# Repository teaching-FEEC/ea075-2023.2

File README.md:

# EA075 - Introdução a Projeto de Sistemas Embarcados

2° Semestre de 2023

Profa. Paula Dornhofer Paro Costa

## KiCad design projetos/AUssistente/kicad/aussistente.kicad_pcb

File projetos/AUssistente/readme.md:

# `AUssistente`
# `Pet Care Assistant`

## Apresentação

O presente projeto foi originado no contexto das atividades da disciplina de graduação *EA075 - Introdução ao Projeto de Sistemas Embarcados*, 
oferecida no segundo semestre de 2023, na Unicamp, sob supervisão da Profa. Dra. Paula Dornhofer Paro Costa, do Departamento de Engenharia de Computação e Automação (DCA) da Faculdade de Engenharia Elétrica e de Computação (FEEC).

## Integrantes

|Nome  | RA | Curso|
|--|--|--|
| Betania Eugenia Rodrigues da Silva  | 167508  | Eng. Elétrica|
| Vinícius de Oliveira Peixoto Rodrigues  | 245294  | Eng. de Computação |

## Descrição do Projeto
> Descrição do objetivo principal do projeto, incluindo contexto gerador, motivação.

O objetivo do presente projeto é desenvolver um sistema que auxilie os donos de animais de estimação, com foco em cães e gatos, a facilitar o monitoramento da saúde de seus pets em tempo real. Esta iniciativa surge em resposta à crescente demanda por cuidados mais especializados e personalizados para nossos queridos animais de estimação, que estão cada vez mais integrados à vida familiar. O sistema atuará como um 'companheiro canino e felino inteligente', oferecendo uma solução completa para monitorar e melhorar o bem-estar de nossos bichinhos, garantindo que eles desfrutem de uma vida feliz e saudável ao nosso lado.

> Qual problema vocês pretendem solucionar?

Nosso projeto tem como objetivo resolver diversos desafios enfrentados pelos donos de animais de estimação. O primeiro grande problema a ser abordado é a perda de animais de estimação quando eles escapam, o que é uma preocupação frequente para muitos proprietários. Para resolver essa questão, haverá um sistema de geolocalização que permite localizar os animais rapidamente, facilitando o reencontro com seus donos.

Além disso, nosso sistema visa melhorar o cuidado com a saúde dos animais de estimação de maneira mais abrangente. Ele monitorará constantemente os batimentos cardíacos dos animais e notificará os proprietários se os batimentos cardíacos saírem do normal, permitindo uma resposta rápida em caso de problemas de saúde. Além do mais, o sistema será capaz de aferir o sono e o padrão de alimentação dos animais, o que ajuda os donos a garantir que seus bichinhos tenham um estilo de vida saudável. Isso não só aumenta a qualidade de vida dos animais de estimação, mas também antecipa possíveis agravantes para sua saúde, permitindo intervenções precoces quando necessário.

> Quem são os potenciais usuários?
 
Donos de animais de estimação em um geral.
 
> É possível estabelecer um valor econômico associado?

Sim, é possível, mas primeiramente é necessário realizar um levantamento dos componentes a serem utilizados.

## Descrição Funcional

### Funcionalidades
- Rastreamento de GPS
- Comunicação via BLE/rede sem fio
- Monitoramento de batimentos cardíacos e oxigenação sanguínea
- Acompanhamento dos Níveis de Atividades
- Aferição de Hábitos Diários como frequência e nutrição das refeições e padrões de sono
- Alertas de saída da área pré determinada pelo dono
- Alertas de temperatura corporal do pet
- Análise dos dados diários através gráficos para melhor entendimento do dono

### Configurabilidade

- Pareamento BLE: o dispositivo pode ser configurado por meio de um botão para se conectar a um dispositivo (smartphone, assistente virtual, etc.) por Bluetooth para transmitir dados
- Perfil de energia: o modo de funcionamento do dispositivo pode ser configurado de modo a controlar o consumo de energia, prolongando assim o tempo de atividade antes de ser necessário carregar o aparelho

### Eventos
- Ativação do botão de ligar/desligar
- Leitura de sensores (feitas por meio de interrupção de hardware): os sensores serão configurados para, em intervalos regulares, reportarem para o microcontrolador os valores medidos. Estimativa dos intervalos de leituras:
    - Sensor inercial (IMU): entre 200ms e 2s
    - Sensor de batimentos cardíacos/oxigenação sanguínea: entre 1s e 10s
    - Sensor de temperatura: entre 15s e 1m
    - Sensor de nível de bateria: entre 15s e 1m
    - GPS: entre 15s e 1m
- Ativação do botão de pareamento BLE
- Requisição recebida por BLE
- Valores críticos de batimento cardíaco/oxigenação/temperatura
- Fuga do pet (saída da área pré-determinada pelo dono)
- Nível crítico de bateria

### Tratamento de Eventos
- Ativação do botão de ligar/desligar
    - Dispositivo desligado ou em _deep sleep_: carrega dados de configuração da memória flash ou da SRAM, realiza o boot e o bringup dos componentes
    - Dispositivo ativo ou _idle_: realiza a rotina de shutdown, escrevendo dados relevantes na memória não-volátil e desligando a placa

- Leitura de sensores: armazena os dados em um buffer circular na memória RAM
    - Caso o buffer circular esteja cheio: armazena os dados na SRAM ou na memória não-volátil

- Ativação do botão de pareamento BLE: executa a rotina de pareamento para se conectar ao smartphone

- Requisição recebida por BLE/rede sem fio: invoca a rotina adequada para responder à requisição de maneira assíncrona (sem interromper o fluxo de leitura de sensores)

- Valores críticos de batimento cardíaco/oxigenação/temperatura e fuga de pet: toca um aviso sonoro e envia uma mensagem de alerta para o dispositivo conectado por Bluetooth/rede wireless (caso haja um)

- Nível crítico de bateria: envia uma mensagem de alerta para o dispositivo conectado por Bluetooth, escreve dados relevantes na SRAM, desativa os sensores e entra em _deep sleep_

## Descrição Estrutural do Sistema

## Especificações

### Especificação Estrutural

#### Tabela de componentes
| Componente    | Descrição | Funcionalidades | Interface de comunicação | Datasheet |
| ----------    | --------- |    ---------    |         ---------        |  -------  |
| ESP32-U4WDH   | Microcontrolador | Wi-Fi + BLE; excelente gerenciamento de energia; suporte a UART/I2C/SPI; memória flash SPI de 4MB integrada | - | [esp32.pdf](datasheets/esp32.pdf) |
| TMP117        | Sensor digital de temperatura | Alta precisão + baixo consumo de energia| I2C | [tmp117.pdf](datasheets;tmp117.pdf) |
| MAX30102      | Oxímetro + sensor de batimentos | Baixo consumo de energia, resistência a estresse mecânico | I2C | [max30102.pdf](datasheets/max30102.pdf) |
| MAX17043      | Medidor de carga de bateria | Baixo consumo de energia, alta precisão de medição | I2C | [max17043.pdf](datasheets/max17043.pdf) |
| BMI270        | Unidade de medida inercial (IMU) de 6 eixos | Baixo consumo de energia; correção de erro integrada em hardware | I2C/SPI | [bmi270.pdf](datasheets/bmi270.pdf) |
| MAX-M10S      | GPS | Baixo consumo de energia, alta precisão, monitoramento contínuo de geoposicionamento | UART/I2C | [max-m10s.pdf](datasheets/max-ma10s.pdf)

#### Características de operação

| Parâmetro | Min. | Típico | Máx. | Unidade |
| --------  |  --  |  --  | ------ |  -----  |
| Tensão de alimentação | 3.0 | 3.3 | 3.6 | V |
| Capacidade de corrente da bateria | 0.5 | - | - | A |
| Temperatura | -30 | - | 125 | °C |

#### Limites absolutos de operação

Estresse acima dos limites da tabela abaixo podem causar dano permanente ao dispositivo.

| Parâmetro | Min. | Máx. | Unidade |
| --------  |  --  |  --  |  -----  |
| Tensão de entrada | -0.3  | 3.6 | V |
| Corrente | - | 1200 | mA |
| Temperatura | -50 | 150 | °C |
| Impacto mecânico | - | 20000 | g |
| Queda livre sobre superfícies rígidas | - | 1.8 | m |

#### Interfaces de periféricos planejadas

Será necessário projetar um barramento I2C com características elétricas adequadas, seguindo as recomendações
da [especificação oficial](https://www.nxp.com/docs/en/user-guide/UM10204.pdf) do protocolo, no qual os periféricos
serão conectados de modo a atuar como targets, com a MCU assumindo o papel de controller.

Será necessário também projetar um _buzzer_ piezoelétrico de modo a tocar os alertas sonoros especificados nos algoritmos
de tratamento de eventos.

### Especificação de Algoritmos 

Para podermos tratar os eventos decorrentes do sistema do AUssistente, desenvolvemos o seguinte algoritmo em pseudocódigo.

```text
AUssistente;
timer_sensor_inercial;
timer_sensor_batimento;
timer_sensor_temperatura;
timer_sensor_bateria;
timer_gps;
buffer_circular;

função principal():
  em caso de evento:
		  processar_evento(evento)

função processar_evento(evento):
  caso evento == evento.botao_ligar:
		  se AUssistente.estado == estado.desligado || AUssistente.estado == estado.hibernar:
      configs = carregar_dados_configuracao( )
      inicializar_componentes(configs)

  senão, se AUssistente.estado == estado.ativo || AUssistente.estado == estado.ocioso:
    salvar_dados( )
    desligar_placa( )

  caso evento == evento.leitura_sensor:
		  dados = ler_sensor(evento.enum_sensor)
    se buffer_circular está cheio:
      salvar_memoria(dados)
		  senão:
      buffer_circular[dados.enum_sensor].proximo(dados.info)

  caso evento == evento.pareamento:
    AUssistente.dispositivo = parear( )

  caso evento == evento.requisicao:
    tratar_requisicao(evento.requisicao)

  caso evento == evento.valores_criticos:
    tocar_aviso_sonoro(evento.valor)
    enviar_mensagem_dispositivo(evento.valor)

  caso evento == evento.bateria_critica:
    enviar_alerta_bateria( )
    salvar_dados( )
    desativar_sensores( )
    hibernar( )

  caso default:
    emitir_erro_evento()

função carregar_dados_configuracao():
  configs = ler_arquivo(caminho_arquivo)
  retornar configs

função inicializar_componentes(configs):
  AUssistente = novo AUssistente;
  novo buffer_circular = [5][configs[tamBuffer]]
  AUssistente.perfil_energia = configs[pEnergia]
  AUssistente.ultimo_dispositivo = configs[ultimoDispositivoConectado]
  AUssistente.sensores_ativos = true
  timer_gps = configs[tGPS] ? configs[tGPS] : 30s
  timer_sensor_bateria = configs[tBateria] ? configs[tBateria] : 30s
  timer_sensor_batimento = configs[tBatimento] ? configs[tBatimento] : 5s
  timer_sensor_inercial = configs[tIMU] ? configs[tIMU] : 1s
  timer_sensor_temperatura = configs[tTemperatura] ? configs[tTemperatura] : 30s
  AUssistente.dispositivo = parear(AUssistente.ultimo_dispositivo)

função salvar_dados():
  escrever(caminho_arquivo, AUssistente, buffer_circular)

função desligar_placa():
  power_off_mode()

função ler_sensor(sensor_id):
  retornar pegar_leitura_sensor(sensor_id)

função salvar_memoria(dados):
  EEPROM.write(dados);

função parear(dispositivo):
  BTSerial.begin(dispositivo.serial)
  sucesso = BTSerial.available()
	 retornar sucesso ? dispositivo : null

função parear():
  device = BTSerial.emparelhar()
	 retornar device

função tratar_requisicao(requisicao):
	 caso requisicao == requisicao.1:
		  tratamento_1()
	 caso requisicao == requisicao.2:
		  tratamento_2()
	 caso default:
		  tratamento_default()

função tocar_aviso_sonoro(tipo):
	 tone(buzzer_pin, tipo * 800)
	 delay(15000)
	 noTone(buzzer_pin)

função enviar_mensagem_dispositivo(tipo):
	 BTSerial.write("Atenção: O " + tipo + " está com valores criticos!")

função enviar_alerta_bateria():
	 BTSerial.write("Atenção: Bateria do AUssistente em niveis criticos, entrando em hibernação...")

função desativar_sensores():
	 AUssistente.sensores_ativos = false

função hibernar():
	 power_save_mode()

```

## Referências (ATUALIZAR SE NECESSÁRIO)
- Especificação do protocolo I2C https://www.nxp.com/docs/en/user-guide/UM10204.pdf
- Cálculos de valores de resistência em barramentos I2C https://www.allaboutcircuits.com/technical-articles/the-i2c-bus-hardware-implementation-details/
- Design de buzzers piezoelétricos https://www.diodes.com/assets/App-Note-Files/Design-Considerations-for-Driving-Piezoelectric-Buzzers.pdf
- Roteamento de bus I2C https://hillmancurtis.com/i2c-pcb-layout/

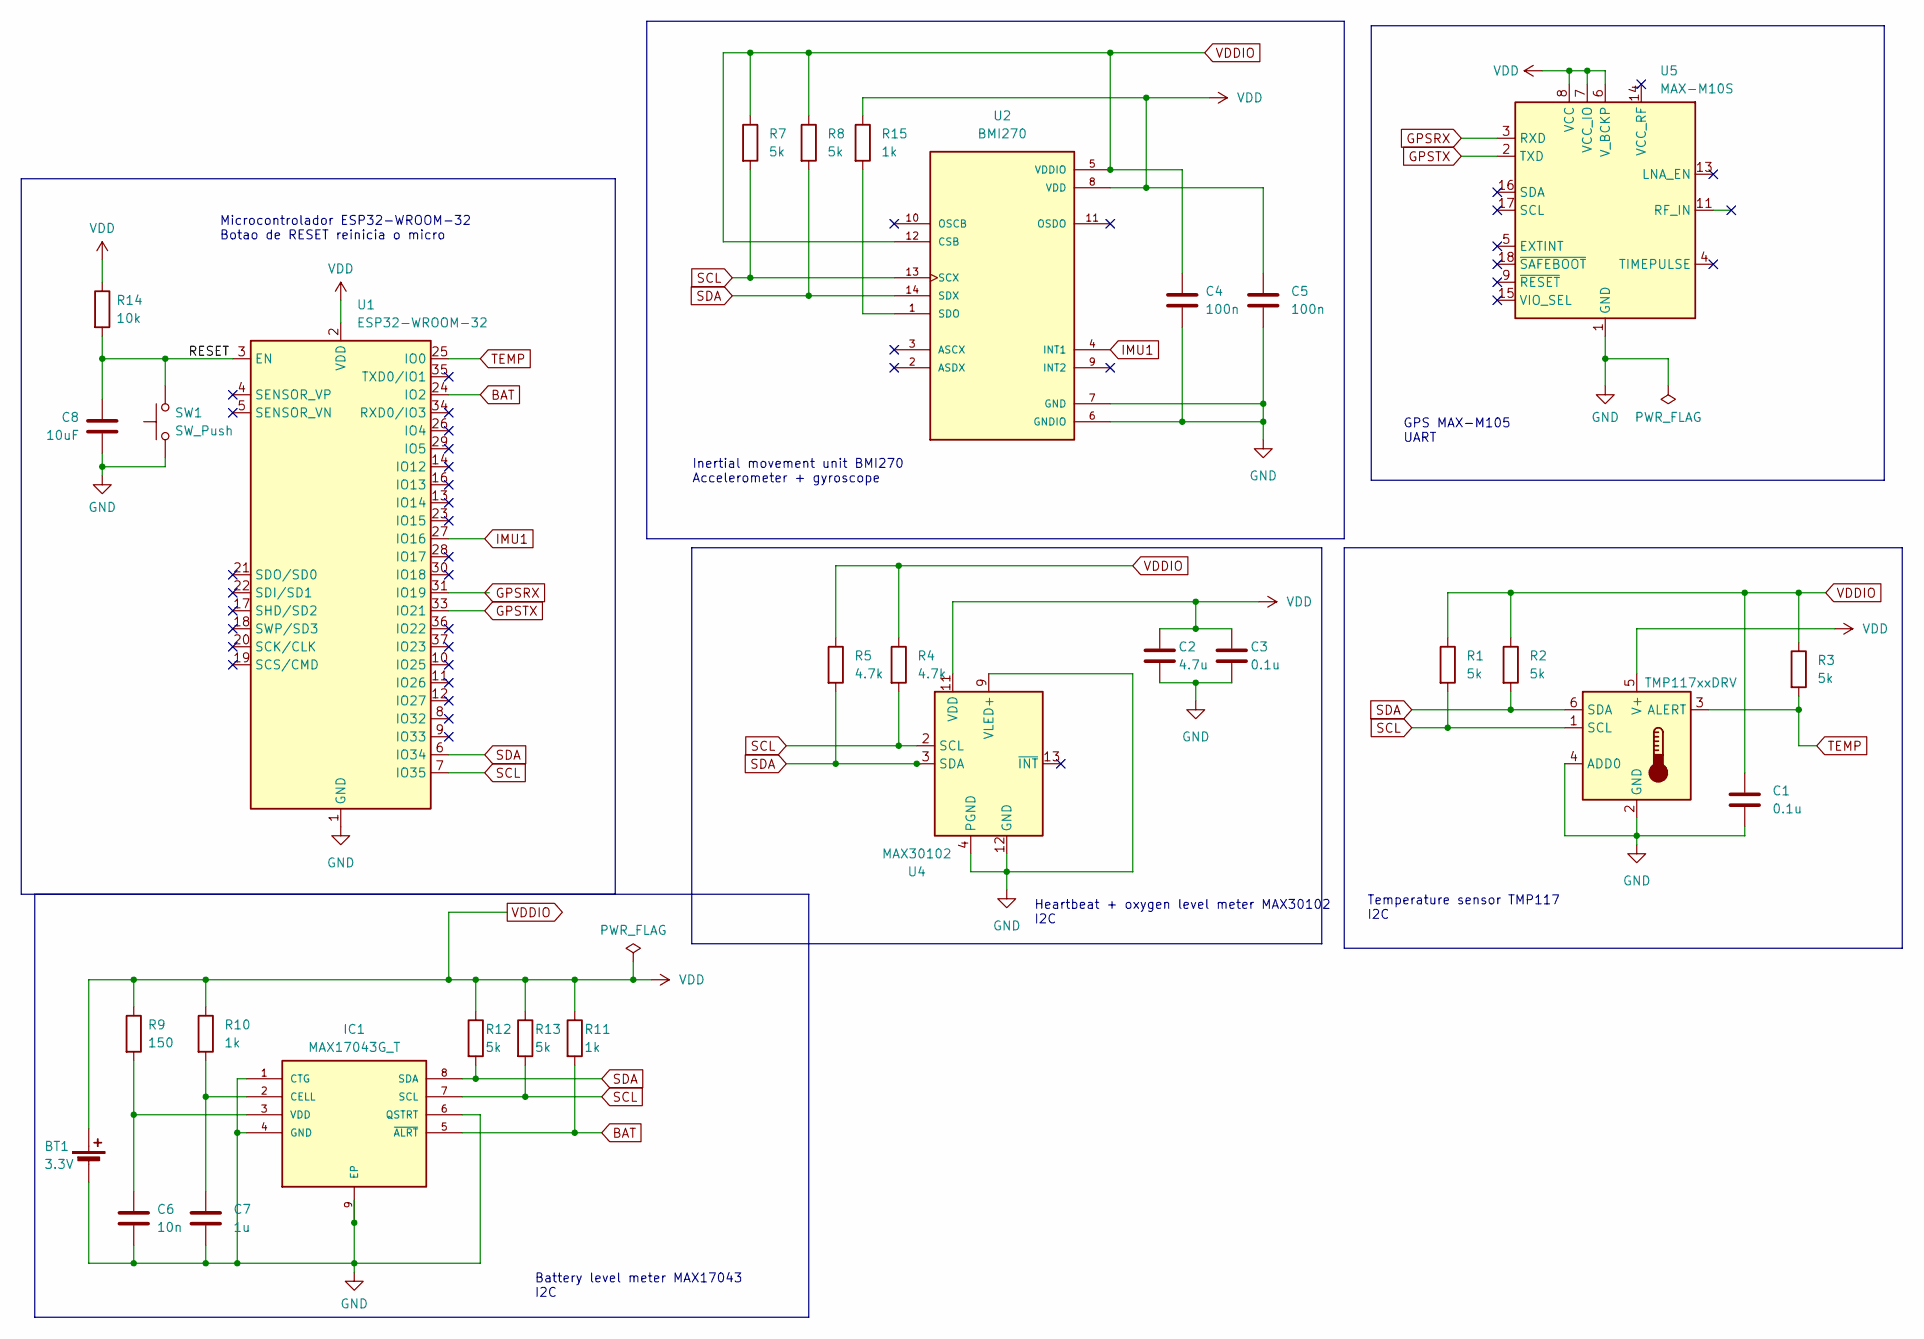
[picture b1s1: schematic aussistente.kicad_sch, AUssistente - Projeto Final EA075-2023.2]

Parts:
BT1: 3.3V; BatteryHolder_Eagle_12BH611-GR
C1, C3: 0.1u; C_0402_1005Metric
C2: 4.7u; C_0402_1005Metric
C4, C5: 100n; C_0402_1005Metric
C6: 10n; C_0402_1005Metric
C7: 1u; C_0402_1005Metric
C8: 10uF; C_0402_1005Metric
IC1: MAX17043G_T; SON50P300X200X80-9N; MOUSER_PART_NUMBER 700-MAX17043G+T; DigiKey_Part_Number 175-MAX17043G+TTR-ND
R1, R2, R3, R7, R8, R12, R13: 5k; R_0201_0603Metric
R4, R5: 4.7k; R_0201_0603Metric
R9: 150; R_0201_0603Metric
R10, R11, R15: 1k; R_0201_0603Metric
R14: 10k; R_0201_0603Metric
SW1: SW_Push; SW_PUSH_6mm_H5mm
U1: ESP32-WROOM-32
U2: BMI270; XDCR_BMI270
U3: TMP117xxDRV; WSON-6-1EP_2x2mm_P0.65mm_EP1x1.6mm
U4: MAX30102; Maxim_OLGA-14_3.3x5.6mm_P0.8mm
U5: MAX-M10S; ublox_MAX

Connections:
/RESET: C8.1, R14.2, SW1.2, U1.3 (EN)
BAT: IC1.5 (~ALRT), R11.2, U1.24 (IO2)
GND: BT1.2 (-), C1.1, C2.2, C3.2, C4.2, C5.2, C6.2, C7.2, C8.2, IC1.1 (CTG), IC1.4 (GND), IC1.6 (QSTRT), IC1.9 (EP), SW1.1, U1.1 (GND), U1.15 (GND), U1.38 (GND), U1.39 (GND), U2.6 (GNDIO), U2.7 (GND), U3.2 (GND), U3.4 (ADD0), U4.4 (PGND), U4.9 (VLED+), U4.10 (VLED+), U4.12 (GND), U5.1 (GND), U5.10 (GND), U5.12 (GND)
GPSRX: U1.31 (IO19), U5.3 (RXD)
GPSTX: U1.33 (IO21), U5.2 (TXD)
IMU1: U1.27 (IO16), U2.4 (INT1)
unnamed: C7.1, IC1.2 (CELL), R10.2
unnamed: C6.1, IC1.3 (VDD), R9.2
unnamed: R15.2, U2.1 (SDO)
SCL: IC1.7 (SCL), R1.2, R4.2, R7.2, R13.2, U1.7 (IO35), U2.13 (SCX), U3.1 (SCL), U4.2 (SCL)
SDA: IC1.8 (SDA), R2.2, R5.2, R8.2, R12.2, U1.6 (IO34), U2.14 (SDX), U3.6 (SDA), U4.3 (SDA)
TEMP: R3.2, U1.25 (IO0), U3.3 (ALERT)
VDDIO: BT1.1 (+), C1.2, C2.1, C3.1, C4.1, C5.1, R1.1, R2.1, R3.1, R4.1, R5.1, R7.1, R8.1, R9.1, R10.1, R11.1, R12.1, R13.1, R14.1, R15.1, U1.2 (VDD), U2.5 (VDDIO), U2.8 (VDD), U2.12 (CSB), U3.5 (V+), U4.11 (VDD), U5.6 (V_BCKP), U5.7 (VCC_IO), U5.8 (VCC)

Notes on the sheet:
Microcontrolador ESP32-WROOM-32 Botao de RESET reinicia o micro
Battery level meter MAX17043 I2C
Heartbeat + oxygen level meter MAX30102 I2C
GPS MAX-M105 UART
Temperature sensor TMP117 I2C
Inertial movement unit BMI270 Accelerometer + gyroscope

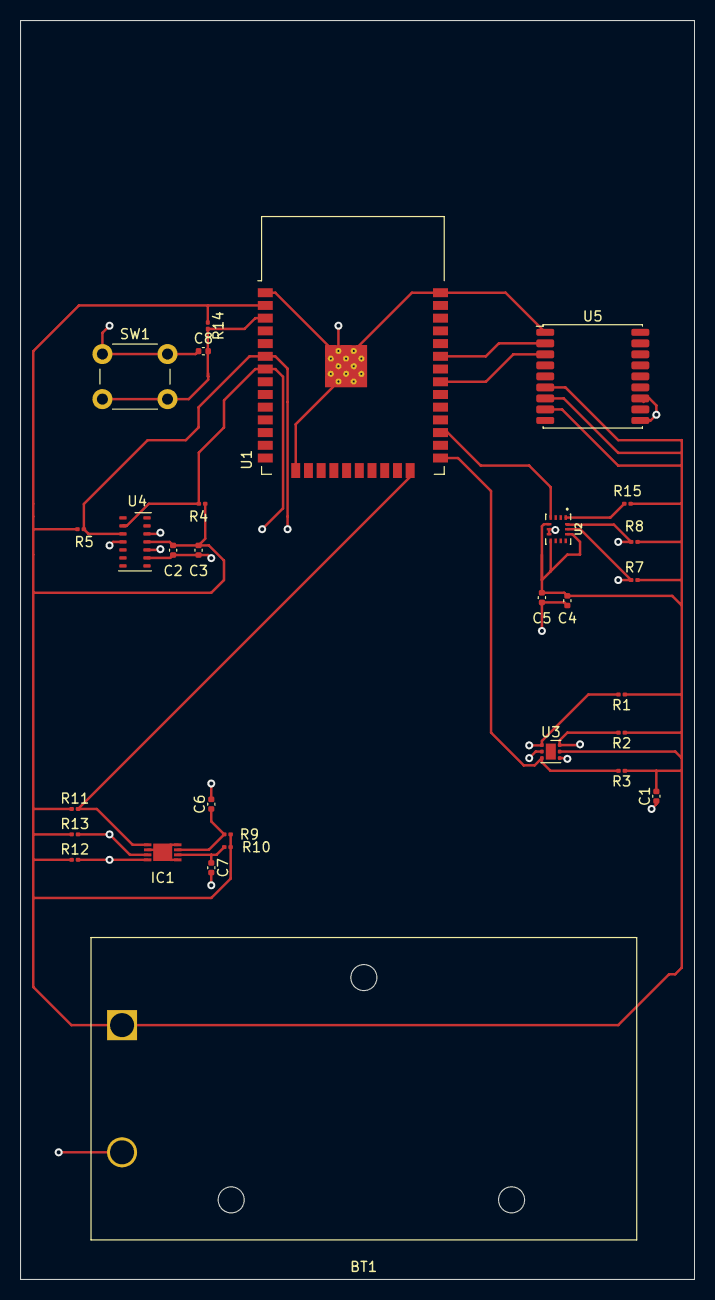
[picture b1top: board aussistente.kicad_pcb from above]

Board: 4 copper layers, 67.3 x 125.7 mm, 30 parts (0 on the bottom side), 13 nets.

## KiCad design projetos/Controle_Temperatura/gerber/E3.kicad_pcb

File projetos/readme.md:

Crie sua pasta de projetos aqui.

Faça edições e adicione arquivos apenas em sua pasta de projetos.

:warning: Não altere este arquivo este arquivo readme.md

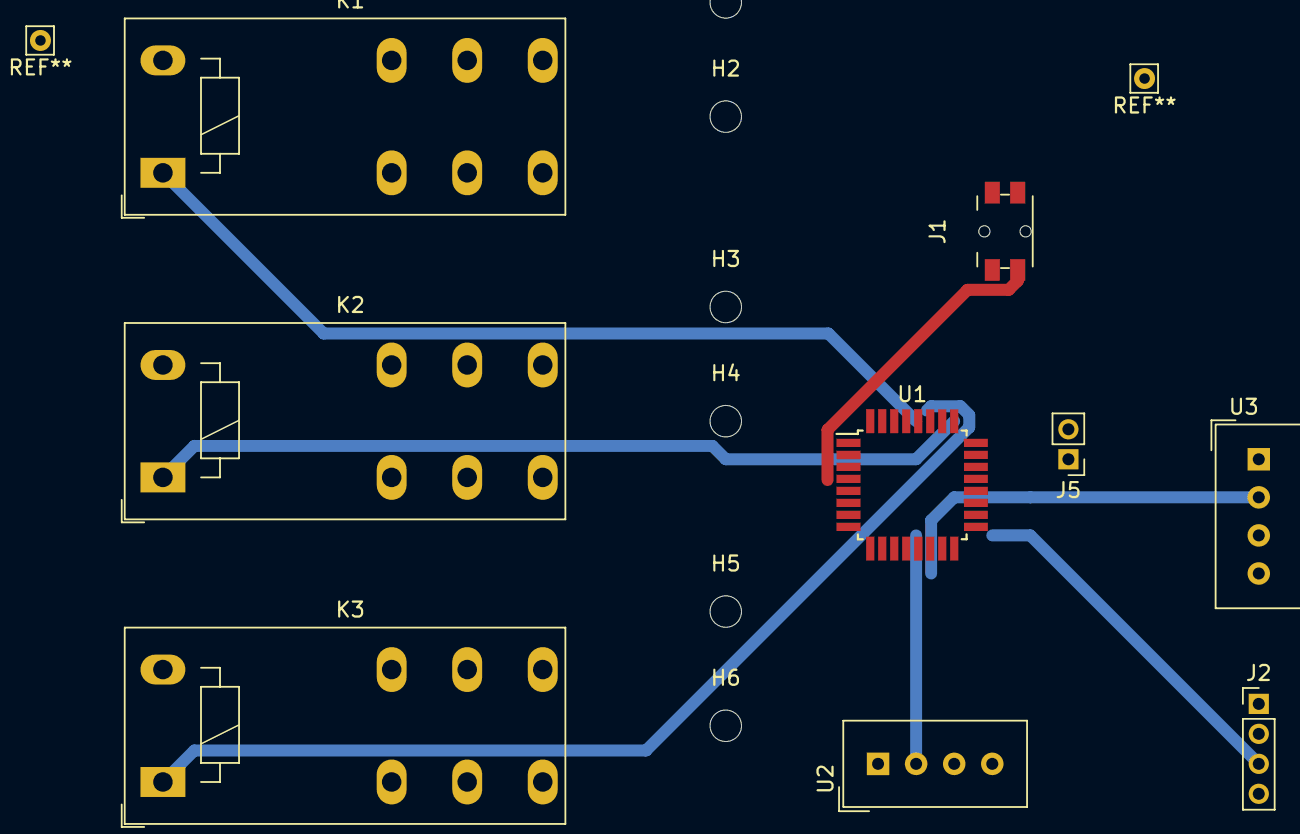
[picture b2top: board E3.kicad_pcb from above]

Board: 4 copper layers, 15 parts (0 on the bottom side), 10 nets.

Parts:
H1: +Motor; MountingHole_2.1mm
H2: -Motor; MountingHole_2.1mm
H3: +Condicionador de Ar; MountingHole_2.1mm
H4: -Condicionador de Ar; MountingHole_2.1mm
H5: +Umidificador; MountingHole_2.1mm
H6: -Umidificador; MountingHole_2.1mm
J1: Botao Iniciar; Panasonic_EVQPUM_EVQPUD
J2: Rain_Inputs; PinHeader_1x04_P2.00mm_Vertical
J5: Sensor fim de curso; PinHeader_1x02_P2.00mm_Vertical
K1, K2, K3: RT314A24; Relay_SPDT_Schrack-RT1-16A-FormC_RM5mm
U1: ATmega328-A; TQFP-32_7x7mm_P0.8mm
U2, U3: DHT11; Aosong_DHT11_5.5x12.0_P2.54mm

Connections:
Earth: J2.2, J5.1, U1.16 (PB4), U2.4 (GND), U3.4 (GND)
unnamed: J1.2, J2.1, J5.2, U1.4 (VCC), U1.6 (VCC), U2.1 (VDD), U3.1 (VDD)
unnamed: K1.A2, K2.A2, K3.A2, U1.3 (GND), U1.5 (GND), U1.21 (GND)
unnamed: J1.1, U1.25 (PC2)
unnamed: J2.3, U1.17 (PB5)
unnamed: U1.12 (PB0), U2.2 (DATA)
unnamed: U1.13 (PB1), U3.2 (DATA)
unnamed: K2.A1, U1.26 (PC3)
unnamed: K1.A1, U1.27 (PC4)
unnamed: K3.A1, U1.28 (PC5)

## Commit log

2023-07-30 Alterações readme para novo semestre
2023-07-30 Alterações readme novo semestre
2023-07-30 Criação de novo readem
2023-07-30 Criação readme exemplo
2023-09-07 Diagrama_black_box.drawio
2023-09-07 Rascunho inicial do README
2023-09-07 Actualizar Diagrama_black_box.drawio
2023-09-07 Adicionado Diagrama_black_box.drawio.png
2023-09-07 Actualizar Diagrama_black_box.drawio.png
2023-09-07 Descrição do Sistema Black Box para entrega 1
2023-09-07 project description and functional description
2023-09-07 fixing spaces
2023-09-07 Adding references
2023-09-07 Correção de formatação, e adiçao de tópicos
2023-09-07 modificando referencias
2023-09-07 Atualizar curso
2023-09-07 adicionando uma referencia
2023-09-07 resolving git problems
2023-09-08 update diagrama
2023-09-08 Create nosso_projeto
2023-09-09 Titulo do projeto
2023-09-09 Descrição_Estrutural.drawio
2023-09-09 inserção do ra e nome
2023-09-09 Adicionado Descrição_Estrutural.drawio
2023-09-09 removendo diagrama antigo
2023-09-10 Inserção da Descrição do projeto, Descrição Funcional, Funcionalidades, Configurabilidade, Eventos e Tratamento de Eventos
2023-09-10 Inserção de quebra de linha
2023-09-10 Update readme.md
    1° edição
2023-09-10 chocadeira.drawio
2023-09-10 Projeto Cobertor Térmico
    Versão inicial
2023-09-10 Commit sem draw.io
2023-09-10 Adicionado chocadeira.drawio.png
2023-09-10 tratamento de eventos e referências
2023-09-10 Entrega 01
2023-09-10 Criando estrutura
2023-09-10 Adicionar evento
2023-09-10 Adicionar tratamento de eventos
2023-09-10 Fix typo
2023-09-10 Add diagram
2023-09-10 Adicionar diagrama
2023-09-10 Add diagram with background
2023-09-10 Create Final Project
2023-09-10 Create Sketch
    First archive
2023-09-10 criar-proj
2023-09-10 Update readme.md and add datasheets
2023-09-10 adicionando descrição estrutural
2023-09-10 Adicionado Descrição_Estrutural.png
2023-09-10 descricao
2023-09-10 econômica
2023-09-10 Update eventos
2023-09-10 tratar display
2023-09-10 Adicionado regador_flowchart.drawio
2023-09-10 Actualizar regador_flowchart.drawio
2023-09-10 Added regador_flowchart.drawio
2023-09-10 Add new events to readme
2023-09-10 Added regador_flowchart.png
2023-09-10 Update refs
2023-09-10 adding refs
2023-09-11 funcionalidades
2023-09-11 configura
2023-09-11 corre
2023-09-11 eventos
2023-09-11 conf
2023-09-11 Update and rename readme.md to ea075-E1.md
    update do texto
2023-09-11 E1-EA075-E1.md
2023-09-11 Add structural diagram
2023-09-11 E1-EA075.md
2023-09-11 2023.1_EA075_E1.md
2023-09-11 upload primeira entrega Beatriz e Emily
2023-09-11 Corrigindo os links
2023-09-12 Rename ea075-E1.md to readme.md
2023-09-13 Arrumando o README do projeto
2023-10-05 Adicionado Especificacao_algoritmo.drawio.png
2023-10-05 Especificação de algoritmos
2023-10-07 Implementa as especificações de hardware e o diagrama de blocos
2023-10-08 especificação do algoritmo: criação de maquina de estados
2023-10-11 Fixing link to fluxograma image
2023-10-14 fix md issues
2023-10-14 img center fix
2023-10-14 definindo estrutura
2023-10-14 alterações no E1 e parte da especificação estrutural
2023-10-14 especificação estrutural
2023-10-14 Remoção da recarga por painel solar
2023-10-14 Atualização do flowchart
2023-10-15 Atualizar regador_flowchart.png
2023-10-15 estrutura finalizada e variáveis de algoritmos definidas
2023-10-15 melhoria na especificação do algoritmos
2023-10-15 entrega 2
2023-10-15 adicionado especificação estrutural
2023-10-15 colocando requisito para facilitar leitura
2023-10-15 corrigindo imagem
2023-10-15 mudando método de display da imagem
2023-10-16 adicionando componentes principais
2023-10-16 adicionando componentes do circuito de atuador
2023-10-16 mudando ordem das colunas
2023-10-16 termino da especificação estrutural
2023-10-16 adicionando valvula solenóide
2023-10-16 Update reademe.md entrega 2
2023-10-16 Rename 2023.1_EA075_E1.md to EA075_E1.md
2023-10-16 Rename ea075-E2-template.md to ea075-E2.md
2023-10-16 atualizando algoritmo
2023-10-30 Adição do pseudocódigo para tratar eventos
2023-10-30 Update readme.md
    P2 projeto
2023-10-30 Update readme.md
    Correção do hiperlink
2023-10-30 Create E2
2023-10-30 (AUssistente) Adicionar especificações de componentes e características funcionais
2023-10-30 Adicionando fluxograma do algorítmo do microcontrolador
2023-10-30 Arrumando imagens do README
2023-10-31 Adicionando push buton e restrições de tempo ao algorítmo
2023-10-31 Renomeando fluxograma do algorítmo
2023-10-31 Especificacao de algoritmos
2023-11-22 Adicionando v1 da função reconhecedora de fala
2023-11-22 Adicionando especificações de uso da função de reconhecimento de fala
2023-11-22 Adicionando mais especificações
2023-11-29 Codigo do projeto adaptado ao Wokwi com ESP32
2023-11-30 adição dos arquivos necessários e descrição dos componentes com os datasheets linkados
2023-11-30 Adiciona arquivos referentes a entrega final
2023-12-01 Updating README file
2023-12-02 descrição do projeto
2023-12-02 Adicionado tempo de sleep antes da nova leitura de bateria
2023-12-02 especificaçao estrutural
2023-12-02 remove datasheet atmega
2023-12-02 attiny43u
2023-12-02 componentes.md adicionados
2023-12-02 alteração nos componentes
2023-12-03 mais alterações nos componentes
2023-12-03 adição de datasheets e componentes
2023-12-03 inserção do algoritmo de leitura de bateria e datasheets
2023-12-03 Comentário sobre o snippet de verifição do nível de bateria
2023-12-03 ajustes datasheet
2023-12-03 novos datasheets nmos e pmos
2023-12-03 Testando outras possibilidades de código para o funcionamento do servo e do reconhecimento de fala
2023-12-03 Create components
2023-12-03 Rename components to components.md
2023-12-03 Create Arquivos_PCB
2023-12-03 Update Arquivos_PCB
2023-12-03 Código do ESP32
2023-12-03 Rename Arquivos_PCB to Arquivos_PCB.md
2023-12-03 Create pdf
2023-12-03 adicao componentes e datasheets
2023-12-04 Rename ea075-E3-template.md to ea075-E3-Final.md
2023-12-04 updating images
2023-12-04 creating componentes.md file
2023-12-04 adding the project images and gerber folders
2023-12-04 Adicionando arquivos da entrega E3
2023-12-04 inserting links to componentes.md file
2023-12-04 finishing the readme file
2023-12-04 adding links
2023-12-04 fixing image
2023-12-04 erro ortográfico
2023-12-04 Revert "E3 Final"
2023-12-04 Update readme.md
    Inclusão so esquemático
2023-12-04 Update readme.md
    Descrição do esquemático
2023-12-04 adding KiCad project in a zip file
2023-12-04 Update readme.md
    correção
2023-12-04 modificaçao no datasheet do indutor pois nao esta conectando pino no pcb
2023-12-04 Create Modulo_sensor
2023-12-04 Create sensor
2023-12-04 Create modulo_central
2023-12-04 Create file
2023-12-04 Create datas
2023-12-04 adding connector info
2023-12-04 fixing paragraph
2023-12-04 criacao das pastas
2023-12-04 Create gerber
2023-12-04 .pdf files for PCI and SCH
2023-12-04 3d model
2023-12-04 add gerber files
2023-12-04 gerber
    gerber
2023-12-04 add bill of material
2023-12-04 Add svg files
2023-12-04 Add kicad project .zip
2023-12-04 atualizanfo components e readme
2023-12-04 Adicionando arquivos do KiCad
2023-12-04 adicionando alterando components
2023-12-04 Atualizando o README
2023-12-04 Corrigindo Descrição Estrutural do sistema
2023-12-04 atualizando diagrama de blocos
2023-12-04 Arrumando árvore do Git
2023-12-04 Arrumando conflitos
2023-12-04 Removendo marcação desnecessária
2023-12-04 Entrega 3
2023-12-05 Add gerber
2023-12-05 Create imagens
2023-12-05 Rename file to file
2023-12-05 Rename sensor to sensor
2023-12-05 Rename projetos/Parking_Monitor/Parking_monitor_specs.pdf to projetos/Parking_Monitor/pdf/Parking_monitor_specs.pdf
2023-12-05 Rename modulo_central.zip to modulo_central.zip
2023-12-05 Rename projeto_sensor.zip to projeto_sensor.zip
2023-12-05 Rename RENDER_parkmonitoring.png to RENDER_parkmonitoring.png
2023-12-05 Rename TRAILS_parkmonitoring.png to TRAILS_parkmonitoring.png
2023-12-05 Rename schemaa_parkmonitoring.png to schemaa_parkmonitoring.png
2023-12-05 Rename sensor_PCB.PNG to sensor_PCB.PNG
2023-12-05 Rename sensor_PCBL1.PNG to sensor_PCBL1.PNG
2023-12-05 Rename sensor_PCBL2.PNG to sensor_PCBL2.PNG
2023-12-05 Rename sensor_model.png to sensor_model.png
2023-12-05 Rename sensor_model2.png to sensor_model2.png
2023-12-05 Rename sensor_model3.PNG to sensor_model3.PNG
2023-12-05 Rename sensor_schema.PNG to sensor_schema.PNG
2023-12-08 Create md
2023-12-09 Revert "Organização das pastas"
2023-12-09 Revert "Piaiman patch 3"
